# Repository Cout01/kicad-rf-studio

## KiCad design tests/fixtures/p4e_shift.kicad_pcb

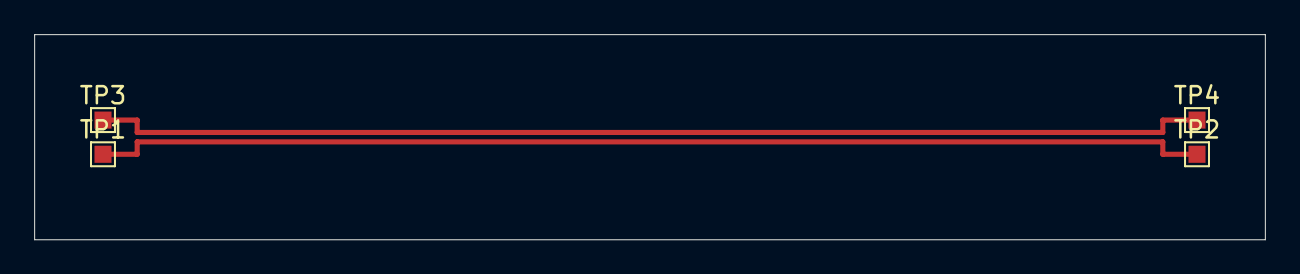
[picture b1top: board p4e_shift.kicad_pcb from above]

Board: 4 copper layers, 72.0 x 12.0 mm, 4 parts (0 on the bottom side), 2 nets.

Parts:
TP1, TP2, TP3, TP4: TP; TestPoint_Pad_1.0x1.0mm

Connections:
D+: TP1.1, TP2.1
D-: TP3.1, TP4.1

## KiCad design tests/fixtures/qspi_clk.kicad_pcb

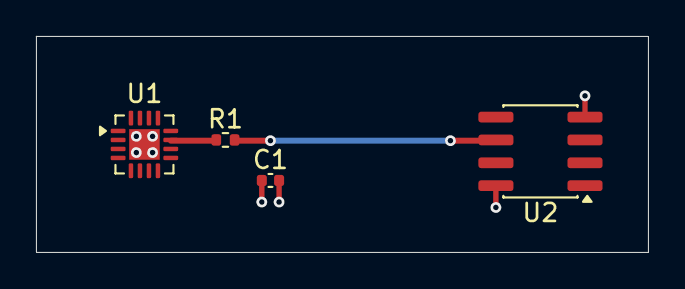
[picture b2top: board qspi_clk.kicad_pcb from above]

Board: 4 copper layers, 34.0 x 12.0 mm, 4 parts (0 on the bottom side), 4 nets.

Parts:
C1: 100nF; C_0402_1005Metric
R1: 33; R_0402_1005Metric
U1: MCU; QFN-16-1EP_3x3mm_P0.5mm_EP1.7x1.7mm
U2: FLASH; SOIC-8_3.9x4.9mm_P1.27mm

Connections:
+3V3: C1.1, U1.16, U2.8
FLASH_CLK: R1.2, U2.6
GND: C1.2, U1.17, U2.4
QSPI_CLK: R1.1, U1.11

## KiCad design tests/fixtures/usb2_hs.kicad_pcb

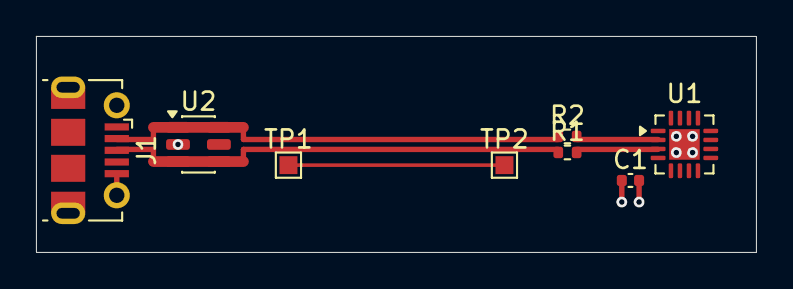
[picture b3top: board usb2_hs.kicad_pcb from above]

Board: 4 copper layers, 40.0 x 12.0 mm, 8 parts (0 on the bottom side), 7 nets.

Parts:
C1: 100nF; C_0402_1005Metric
J1: USB_B_Micro; USB_Micro-B_Molex-105017-0001
R1, R2: 22; R_0402_1005Metric
TP1, TP2: TP; TestPoint_Pad_1.0x1.0mm
U1: MCU; QFN-16-1EP_3x3mm_P0.5mm_EP1.7x1.7mm
U2: USBLC6-2SC6; SOT-23-6

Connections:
AUX: TP1.1, TP2.1
GND: C1.2, J1.5, J1.6, U1.17, U2.2
MCU_D+: R1.2, U1.3
MCU_D-: R2.2, U1.2
USB_D+: J1.3, R1.1, U2.3, U2.4
USB_D-: J1.2, R2.1, U2.1, U2.6
VBUS: J1.1, U2.5
